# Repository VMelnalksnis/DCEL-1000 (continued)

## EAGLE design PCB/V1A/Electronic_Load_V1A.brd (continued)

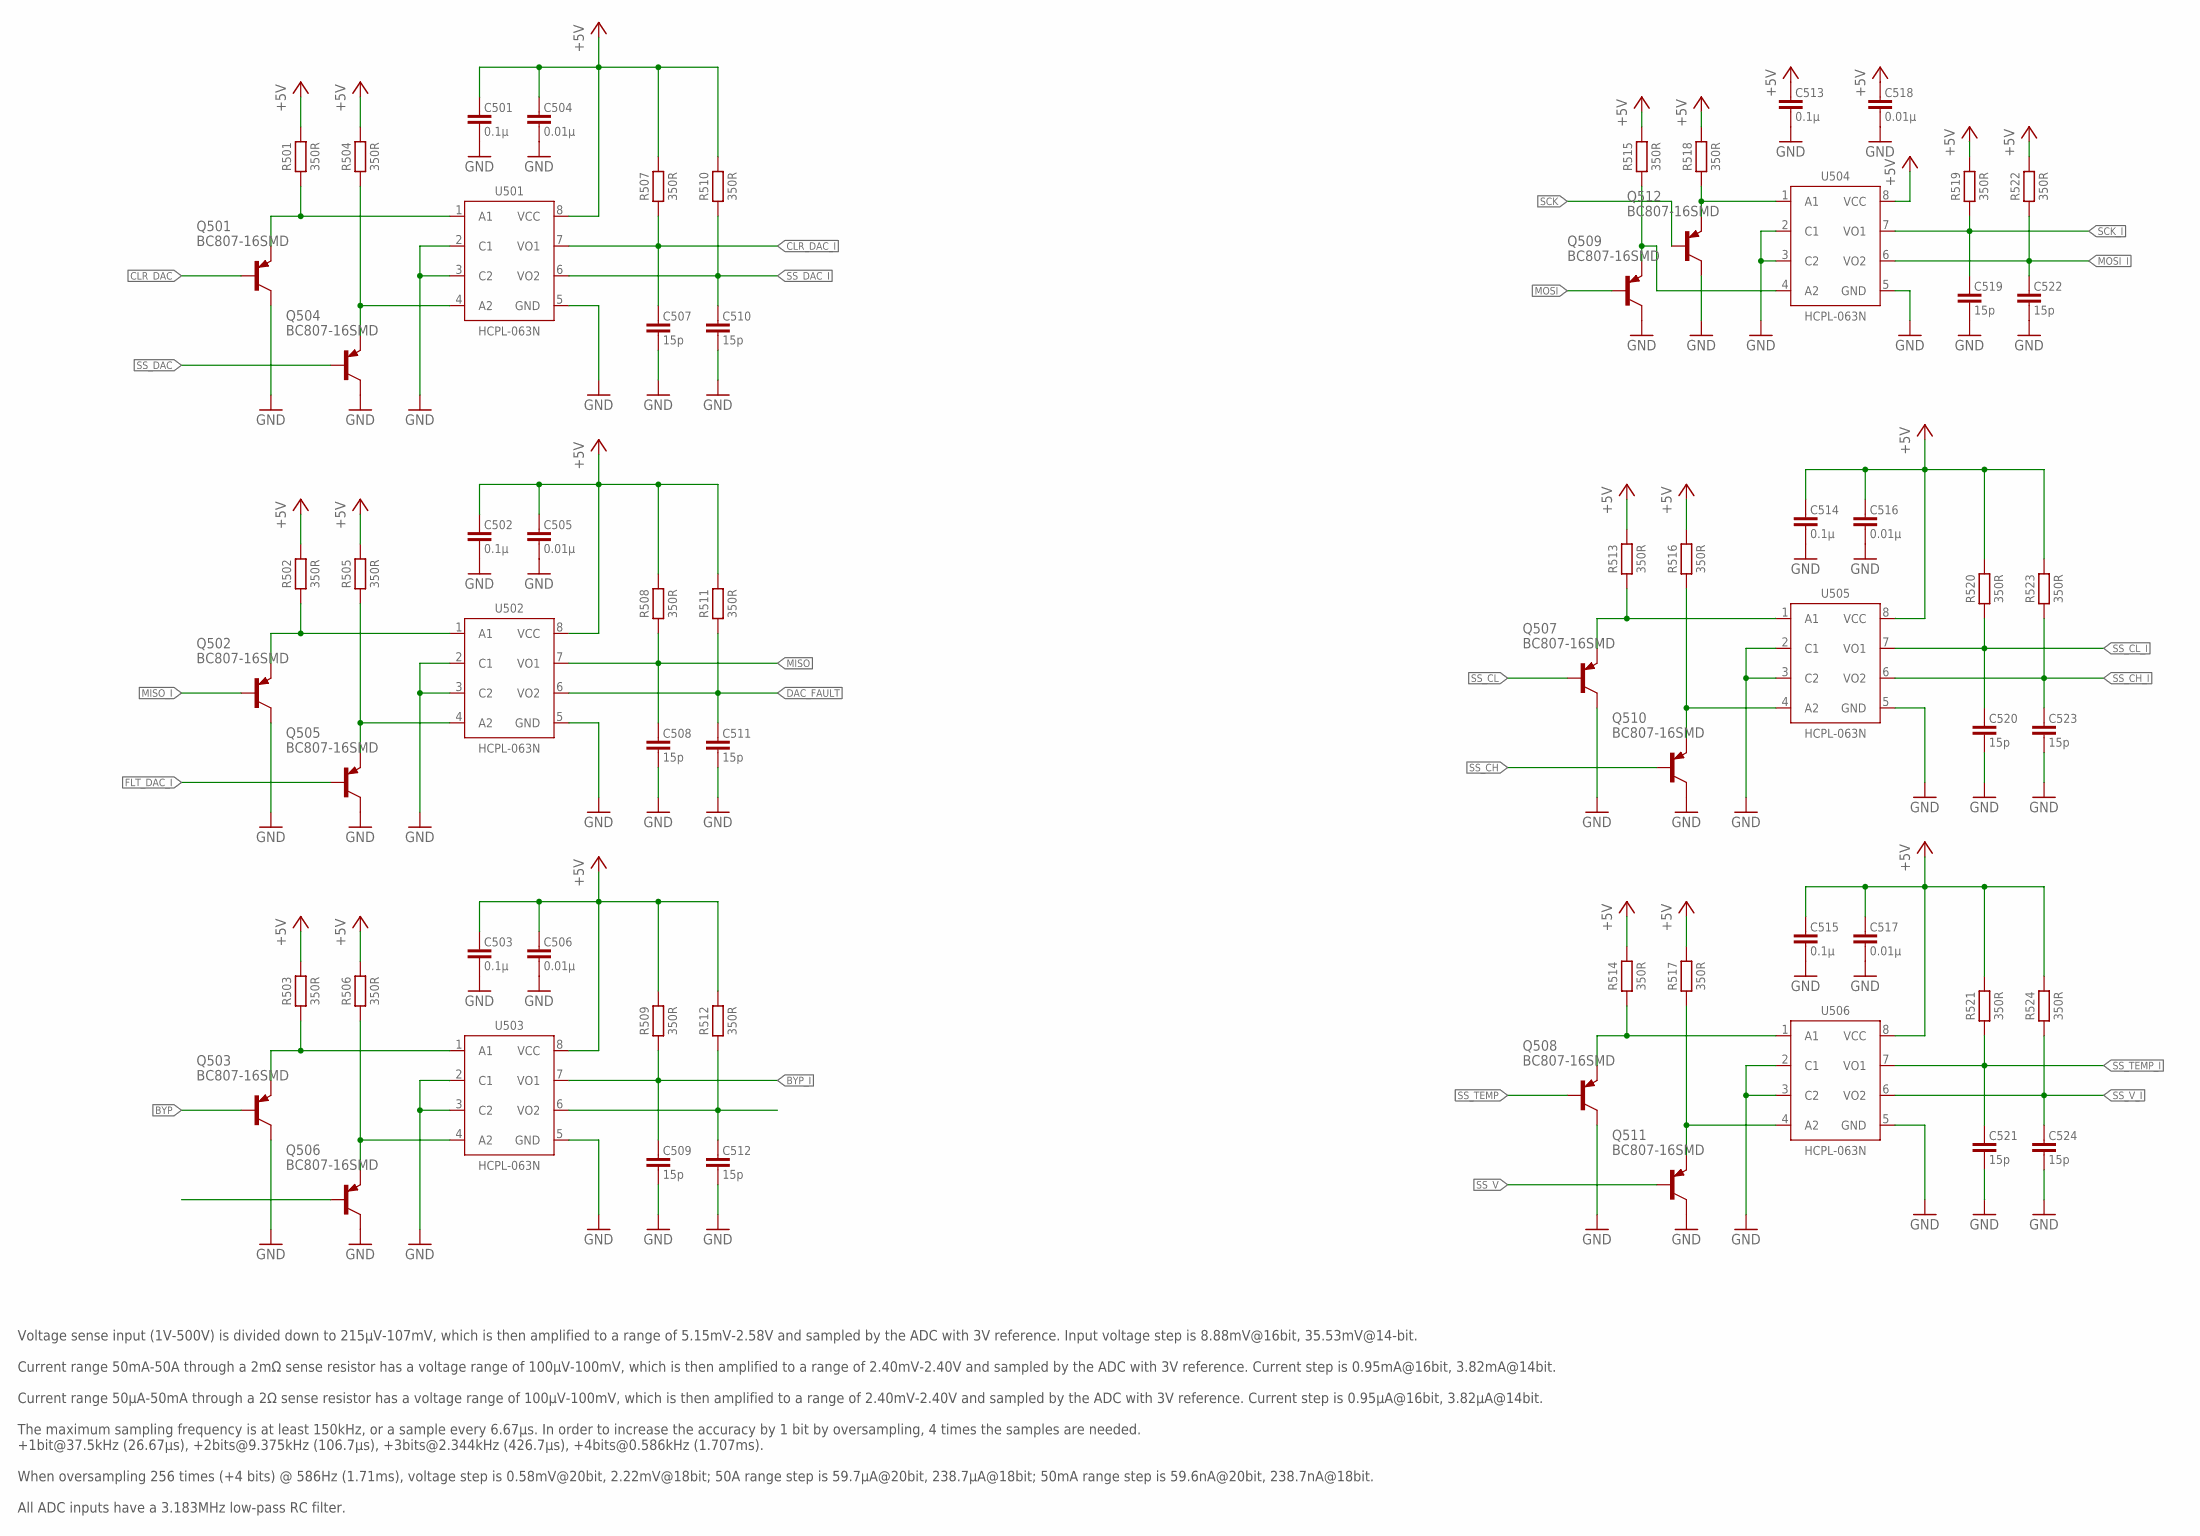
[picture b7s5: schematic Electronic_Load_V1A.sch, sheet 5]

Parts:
C501, C502, C503, C513, C514, C515: 0.1µ; C3216
C504, C505, C506, C516, C517, C518: 0.01µ; C3216
C507, C508, C509, C510, C511, C512, C519, C520, C521, C522, C523, C524: 15p; C1608
Q501, Q502, Q503, Q504, Q505, Q506, Q507, Q508, Q509, Q510, Q511, Q512: BC807-16SMD; SOT23-BEC
R501, R502, R503, R504, R505, R506, R507, R508, R509, R510, R511, R512, R513, R514, R515, R516, R517, R518, R519, R520, R521, R522, R523, R524: 350R; R1608
U501, U502, U503, U504, U505, U506: HCPL-063N; SO8

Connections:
+5V: C501.1, C502.1, C503.1, C504.1, C505.1, C506.1, C513.1, C514.1, C515.1, C516.1, C517.1, C518.1, R501.2, R502.2, R503.2, R504.2, R505.2, R506.2, R507.2, R508.2, R509.2, R510.2, R511.2, R512.2, R513.2, R514.2, R515.2, R516.2, R517.2, R518.2, R519.2, R520.2, R521.2, R522.2, R523.2, R524.2, U501.8 (VCC), U502.8 (VCC), U503.8 (VCC), U504.8 (VCC), U505.8 (VCC), U506.8 (VCC); also elsewhere on the board
BYP: Q503.B
BYP_I: C509.1, R509.1, U503.7 (VO1); also elsewhere on the board
CLR_DAC: Q501.B
CLR_DAC_I: C507.1, R507.1, U501.7 (VO1); also elsewhere on the board
DAC_FAULT: C511.1, R511.1, U502.6 (VO2)
FLT_DAC_I: Q505.B; also elsewhere on the board
GND: C501.2, C502.2, C503.2, C504.2, C505.2, C506.2, C507.2, C508.2, C509.2, C510.2, C511.2, C512.2, C513.2, C514.2, C515.2, C516.2, C517.2, C518.2, C519.2, C520.2, C521.2, C522.2, C523.2, C524.2, Q501.C, Q502.C, Q503.C, Q504.C, Q505.C, Q506.C, Q507.C, Q508.C, Q509.C, Q510.C, Q511.C, Q512.C, U501.2 (C1), U501.3 (C2), U501.5 (GND), U502.2 (C1), U502.3 (C2), U502.5 (GND), U503.2 (C1), U503.3 (C2), U503.5 (GND), U504.2 (C1), U504.3 (C2), U504.5 (GND), U505.2 (C1), U505.3 (C2), U505.5 (GND), U506.2 (C1), U506.3 (C2), U506.5 (GND); also elsewhere on the board
MISO: C508.1, R508.1, U502.7 (VO1)
MISO_I: Q502.B; also elsewhere on the board
MOSI: Q509.B
MOSI_I: C522.1, R522.1, U504.6 (VO2); also elsewhere on the board
unnamed: Q512.E, R518.1, U504.1 (A1)
unnamed: Q507.E, R513.1, U505.1 (A1)
unnamed: Q509.E, R515.1, U504.4 (A2)
unnamed: Q510.E, R516.1, U505.4 (A2)
unnamed: Q508.E, R514.1, U506.1 (A1)
unnamed: Q511.E, R517.1, U506.4 (A2)
unnamed: Q502.E, R502.1, U502.1 (A1)
unnamed: Q505.E, R505.1, U502.4 (A2)
unnamed: Q503.E, R503.1, U503.1 (A1)
unnamed: Q506.E, R506.1, U503.4 (A2)
unnamed: C512.1, R512.1, U503.6 (VO2)
unnamed: Q501.E, R501.1, U501.1 (A1)
unnamed: Q504.E, R504.1, U501.4 (A2)
SCK: Q512.B
SCK_I: C519.1, R519.1, U504.7 (VO1); also elsewhere on the board
SS_CH: Q510.B
SS_CH_I: C523.1, R523.1, U505.6 (VO2); also elsewhere on the board
SS_CL: Q507.B
SS_CL_I: C520.1, R520.1, U505.7 (VO1); also elsewhere on the board
SS_DAC: Q504.B
SS_DAC_I: C510.1, R510.1, U501.6 (VO2); also elsewhere on the board
SS_TEMP: Q508.B
SS_TEMP_I: C521.1, R521.1, U506.7 (VO1); also elsewhere on the board
SS_V: Q511.B
SS_V_I: C524.1, R524.1, U506.6 (VO2); also elsewhere on the board

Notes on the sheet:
Voltage sense input (1V-500V) is divided down to 215µV-107mV, which is then amplified to a range of 5.15mV-2.58V and sampled by the ADC with 3V reference. Input voltage step is 8.88mV@16bit, 35.53mV@14-bit. Current range 50mA-50A through a 2mΩ sense resistor has a voltage range of 100µV-100mV, whic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

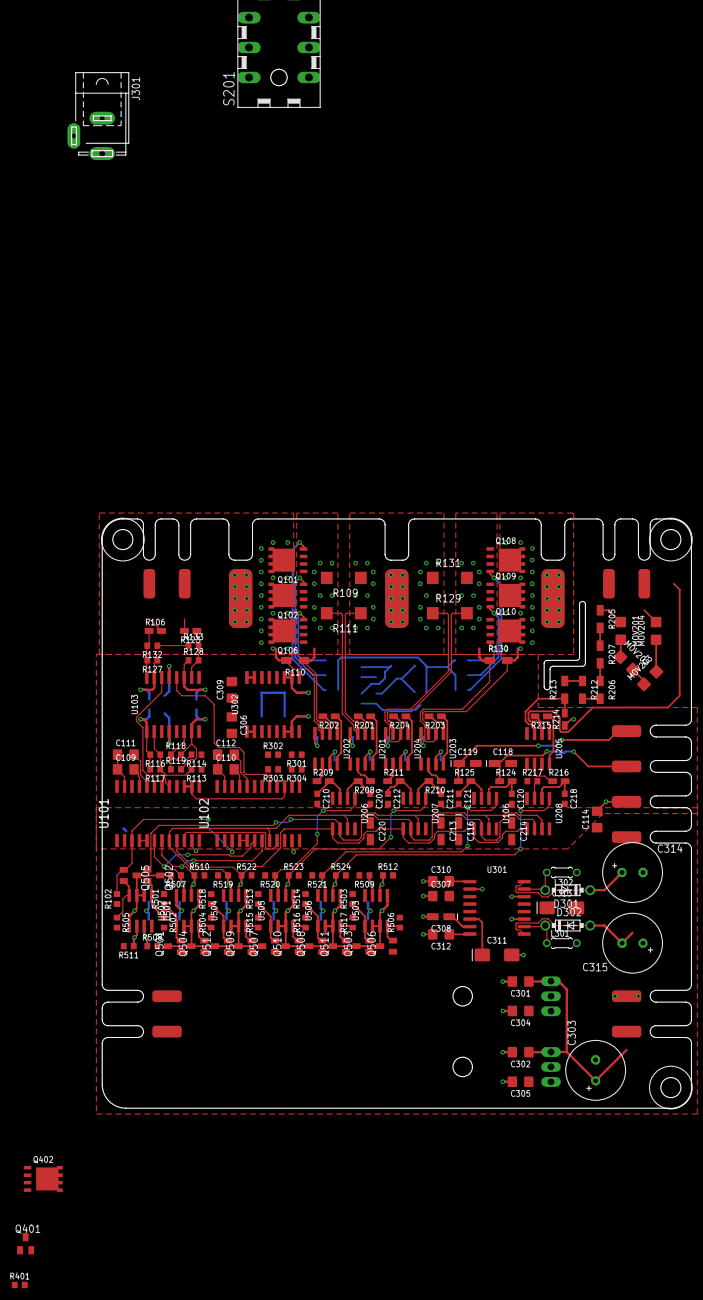
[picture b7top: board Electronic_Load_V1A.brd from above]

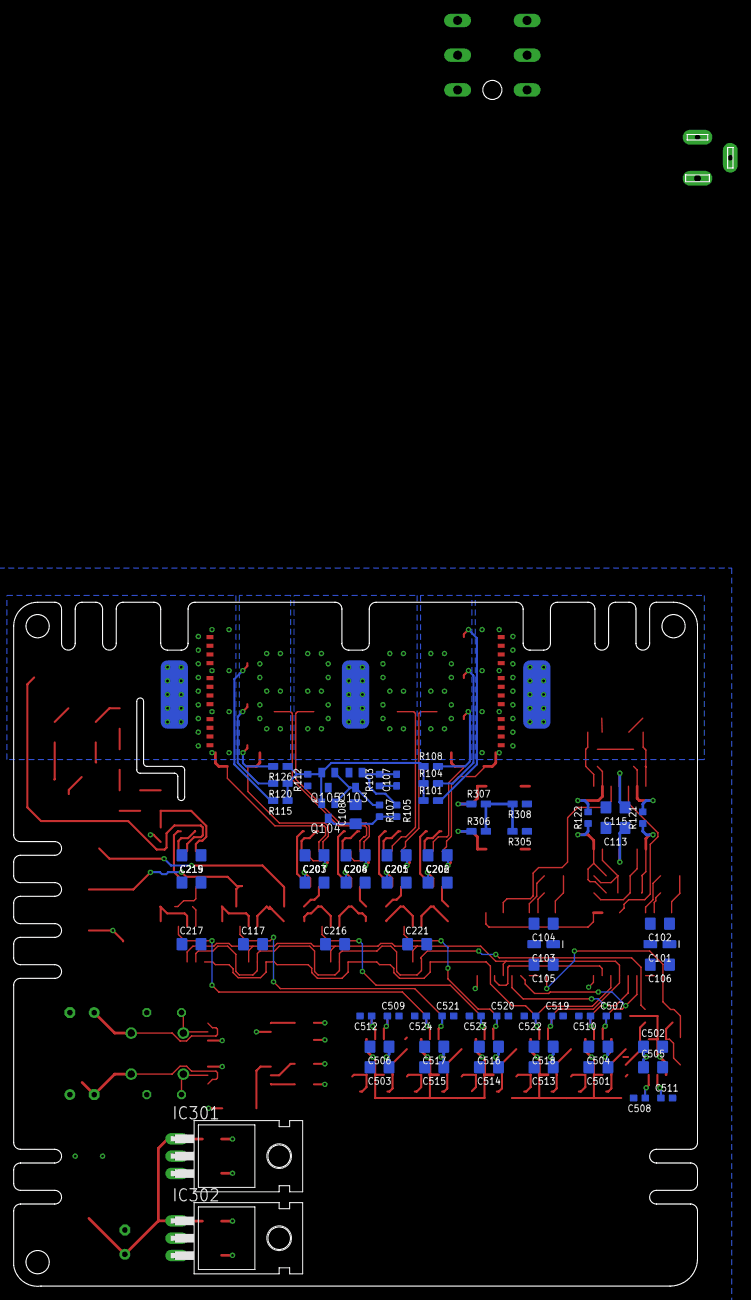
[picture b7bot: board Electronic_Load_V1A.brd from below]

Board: 2 copper layers, 100.0 x 100.0 mm, 240 parts (72 on the bottom side), 114 nets.

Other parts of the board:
U$1, U$2, U$5: M3

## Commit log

2018-05-10 :neckbeard: Added .gitattributes & .gitignore files
2018-05-10 Added buffer amplifiers
2018-05-12 Added docs
2018-05-12 Updated DAC buffer amps & datasheets
    Changed the positive supply of DAC buffer op amps from +5V to +12V, added input offset trimming and set their gain to 2 (1.98). This was done in order to achieve maximum current at low voltages by in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
2018-05-16 Added MOSFET models, updated info
2018-05-18 Added voltage regulators
2018-05-18 Changed measurement opamps to OPA77
2018-05-20 Created board layout, added info
2018-05-21 Board layout work
2018-05-22 Board layout work
    PCB is 100x100mm 2 layer 2oz. MOSFETs mounted between a plate and heatsinks, control board mounted under the plate. DUT+ connected directly from binding post to drains, gates and sources connected to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
2018-05-23 Added temp sensors
2018-05-23 Changed packages, board layout
    Changed component packages and values to the ones that are available. Moved the heatsink mount back to the PCB,
2018-05-24 Updated part list
2018-05-25 Changed OPA77 to AD620
2018-05-25 Added optocouplers
2018-05-25 Removed board layout, updated schematic layout
2018-05-27 Schematic & layout work; added block diagram
2018-05-27 Added heatsink models, ADC/DAC layout
2018-05-28 ADC/DAC board layout
2018-05-29 Board layout
2018-05-30 Backlink to CADLAB.io has been added.
2018-05-31 Board layout, added remote sense input protection
2018-06-04 Added display layout
2018-06-04 Updated schematic
2018-06-10 Removed external parts from PCB, added Front Panel PCB
2018-07-27 Added Gate driver simulation
2018-08-03 Simulation, layout & info - V4A
2018-08-07 Added optoisolation to MOSFET board
2018-08-11 Changed to single board design
2018-08-17 PCB layout
2018-08-21 Added block diagram
2018-08-22 PCB layout, cleaned part list
2018-08-23 Updated ,gitattributes
2018-08-23 Updated .gitattributes
    Trying to fix language detection for LTSpice files.
2018-08-23 Removed abandoned PCB attempts
2018-08-23 Finalizing components & placement
2018-08-24 Cleaned DOCS
2018-08-28 PCB layout & simulation
    Added capacitance multiplier to +/-15V rails
2018-08-30 Finished first pass routing/layout
2018-09-07 PCB layout
    Added some copper pours.
2018-09-28 Added power amp for load MOSFET gate
2018-09-29 Gate driver simulations
2018-10-04 Changed load path layout
2018-10-05 Cleaned up schematic; PCB layout
2018-10-08 Schematic layout
2019-03-31 Added V2A board/schematic
2019-04-06 V2A fully routed
